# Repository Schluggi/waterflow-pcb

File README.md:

# waterflow-pcb

## Description
I love the idea of GreatScott`s [Online Water Tracker](https://www.youtube.com/watch?v=BNK92ep8DhY), but unfortunately
it was really difficult for me to implement his circuit on a perfboard, so I designed a cheap PCB for this.

> Please notice, that this board does not replace/include the charge circuit (TP4056) or the boost converter. It
> only replaces the big ESP circuit.

The PCB has also some improvements:
- Connection terminals to easily (dis)connect everything
- Extra connection for a waterflow-sensors [with a temperature sensor](https://smile.amazon.de/gp/product/B07QNN1N7W/ref=ppx_yo_dt_b_asin_title_o04_s01)

## Images

## How to order?
Before you order the PCB, make sure you have all the needed components. You can find them
[here](https://www.instructables.com/Online-Water-Tracker-Reduce-Shower-Time/). Also don't forget to 3d print the case.

Ready? Let's go. I always order my PCBs via [JLCPCB](https://jlcpcb.com), a chinese PCB manufacturer.
1. Create an account
2. Click "Order now"
3. Upload the zip file located inside the [manufactoring](manufactoring) directory
4. Optional: Choose a different color, an ECO-friendly lead-free surface finish and check that no order number is 
printed on the PCB (for aesthetic reasons).

After all you got 5 PCBs for less than 10€. 

## Questions
Just open an issue :)

## Credits 
Created and maintained by Lukas Schulte-Tickmann / Schluggi.

Inspired by [GreatScott](https://www.instructables.com/member/GreatScottLab/).

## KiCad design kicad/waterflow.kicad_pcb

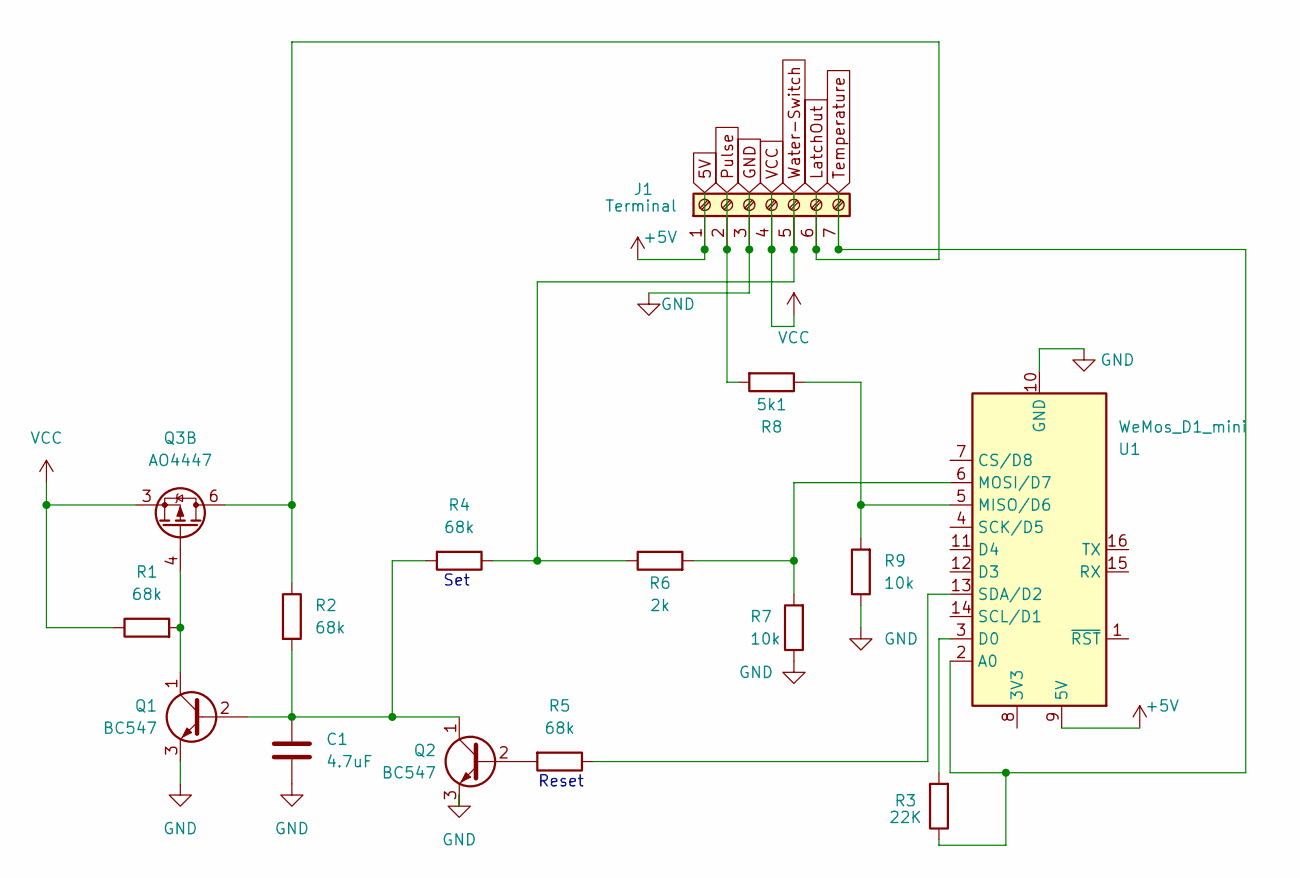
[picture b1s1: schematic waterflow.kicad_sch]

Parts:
C1: 4.7uF; C_Disc_D4.3mm_W1.9mm_P5.00mm
J1: Terminal; TerminalBlock_Phoenix_MKDS-3-7-5.08_1x07_P5.08mm_Horizontal
Q1, Q2: BC547; TO-92_HandSolder
Q3: AO4447; SOIC-8_3.9x4.9mm_P1.27mm
R1, R2, R4, R5: 68k; R_Axial_DIN0207_L6.3mm_D2.5mm_P10.16mm_Horizontal
R3: 22K; R_Axial_DIN0207_L6.3mm_D2.5mm_P10.16mm_Horizontal
R6: 2k; R_Axial_DIN0207_L6.3mm_D2.5mm_P10.16mm_Horizontal
R7, R9: 10k; R_Axial_DIN0207_L6.3mm_D2.5mm_P10.16mm_Horizontal
R8: 5k1; R_Axial_DIN0207_L6.3mm_D2.5mm_P10.16mm_Horizontal
U1: WeMos_D1_mini; WEMOS_D1_mini_light

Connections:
5V: J1.1, U1.9 (5V)
GND: C1.2, J1.3, Q1.3 (E), Q2.3 (E), R7.1, R9.1, U1.10 (GND)
LatchOut: J1.6, Q3.5 (D), Q3.6 (D), R2.1
unnamed: C1.1, Q1.2 (B), Q2.1 (C), R2.2, R4.2
unnamed: Q1.1 (C), Q3.4 (G), R1.2
unnamed: Q2.2 (B), R5.2
unnamed: R3.2, U1.3 (D0)
unnamed: R5.1, U1.13 (SDA/D2)
unnamed: R6.2, R7.2, U1.6 (MOSI/D7)
unnamed: R8.1, R9.2, U1.5 (MISO/D6)
Pulse: J1.2, R8.2
Temperature: J1.7, R3.1, U1.2 (A0)
VCC: J1.4, Q3.3 (1), R1.1
Water-Switch: J1.5, R4.1, R6.1

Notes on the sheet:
Set
Reset

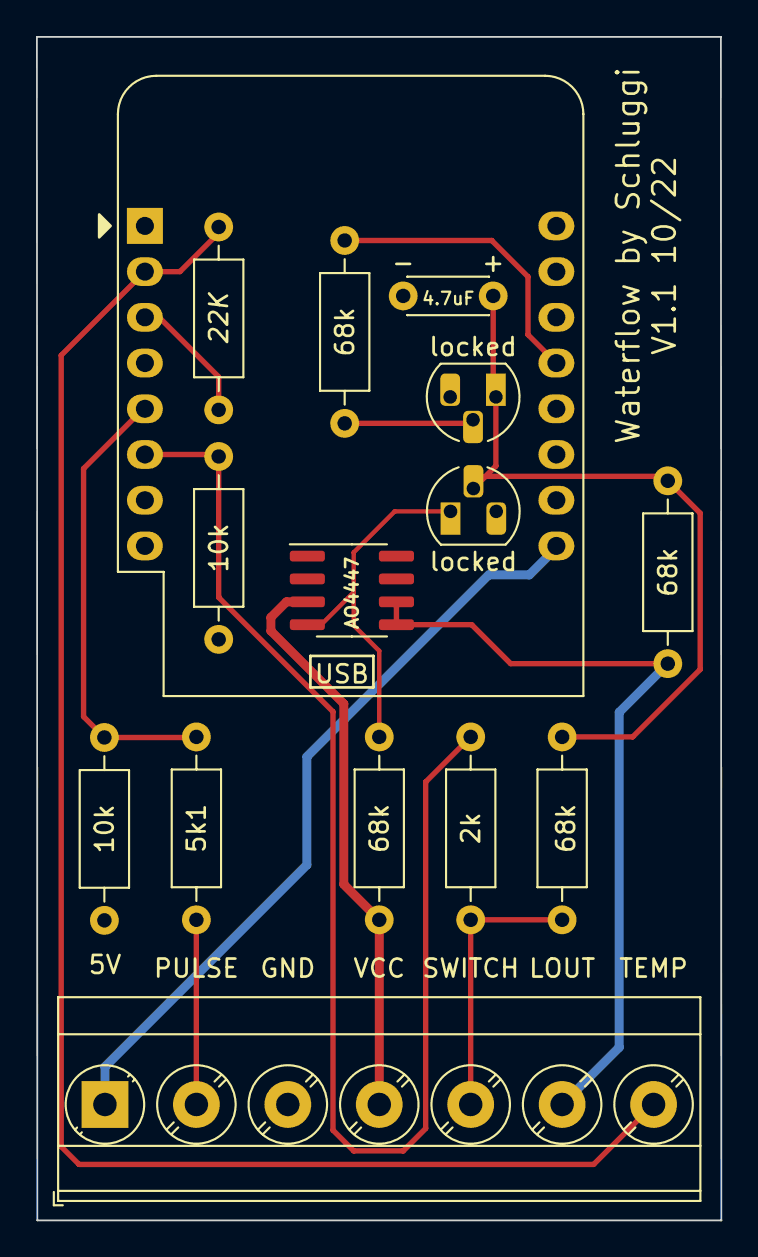
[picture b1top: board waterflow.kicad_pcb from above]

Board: 2 copper layers, 38.0 x 65.8 mm, 15 parts (0 on the bottom side), 14 nets.

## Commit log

2022-09-16 first release
2022-09-16 added: circuit note in readme
2022-09-25 fixed: LED+ is now LOUT
2022-09-25 added: polarity labels for C1
2022-09-25 changed: footprint for BC547 (make soldering easier)
2022-09-25 removed: duplicated connector label
2022-09-28 added: usb label for orientation
2022-09-28 changed: label 3V3 -> VCC
2022-10-03 added: images for v1.1
2022-10-03 added: some kicad files to ignore
2022-10-03 release v1.1
2022-10-14 removed: untested notice, because v1.1 is now tested and works absolutely perfect.
2022-10-14 fixed: PCB improvement text
2022-10-20 fix some typos

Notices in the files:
README.md:
License: MIT
